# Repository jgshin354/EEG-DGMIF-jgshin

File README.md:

# EEG-DGMIF-jgshin
 EEG-DGMIF-jgshin

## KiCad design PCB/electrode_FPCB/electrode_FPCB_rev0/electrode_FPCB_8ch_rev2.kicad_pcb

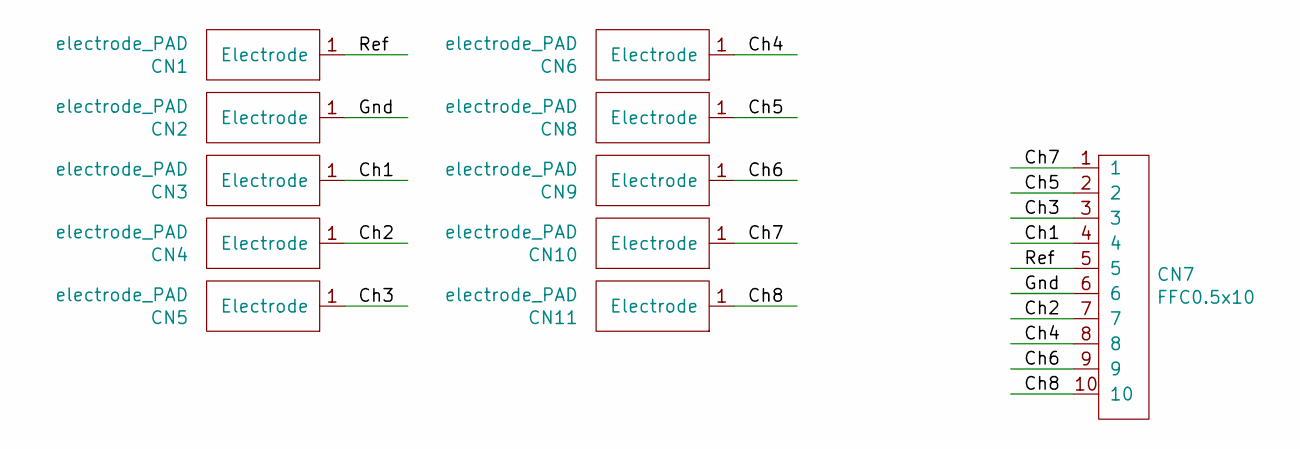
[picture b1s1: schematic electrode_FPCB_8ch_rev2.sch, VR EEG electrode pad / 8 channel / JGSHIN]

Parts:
CN1, CN2, CN3, CN4, CN5, CN6, CN8, CN9, CN10, CN11: electrode_PAD
CN7: FFC0.5x10; FFC cable 0.5 x 10

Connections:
/Ch1: CN3.1, CN7.4
/Ch2: CN4.1, CN7.7
/Ch3: CN5.1, CN7.3
/Ch4: CN6.1, CN7.8
/Ch5: CN7.2, CN8.1
/Ch6: CN7.9, CN9.1
/Ch7: CN7.1, CN10.1
/Ch8: CN7.10, CN11.1
/Gnd: CN2.1, CN7.6
/Ref: CN1.1, CN7.5

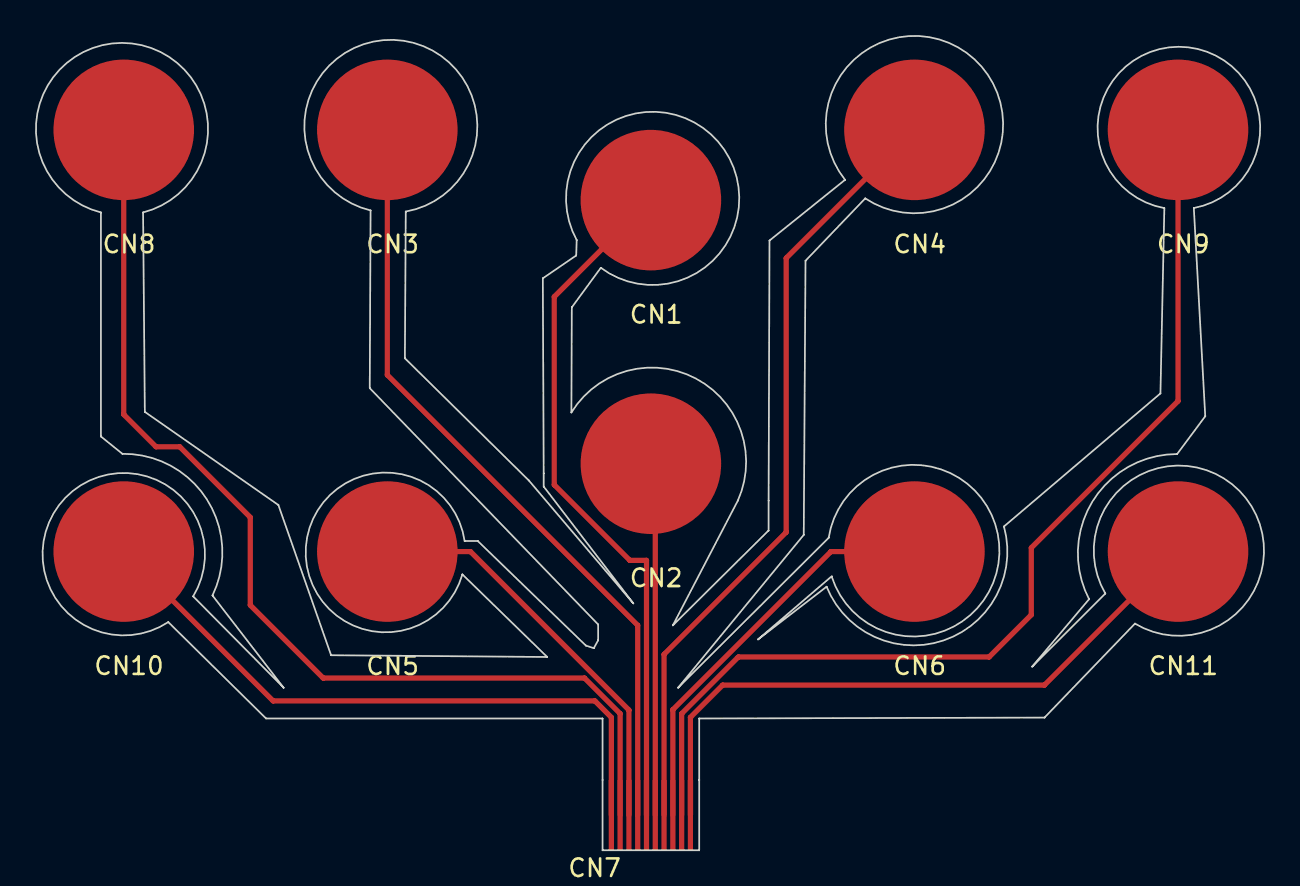
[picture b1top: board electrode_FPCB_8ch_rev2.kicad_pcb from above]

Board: 2 copper layers, 69.9 x 46.3 mm, 11 parts (0 on the bottom side), 10 nets.

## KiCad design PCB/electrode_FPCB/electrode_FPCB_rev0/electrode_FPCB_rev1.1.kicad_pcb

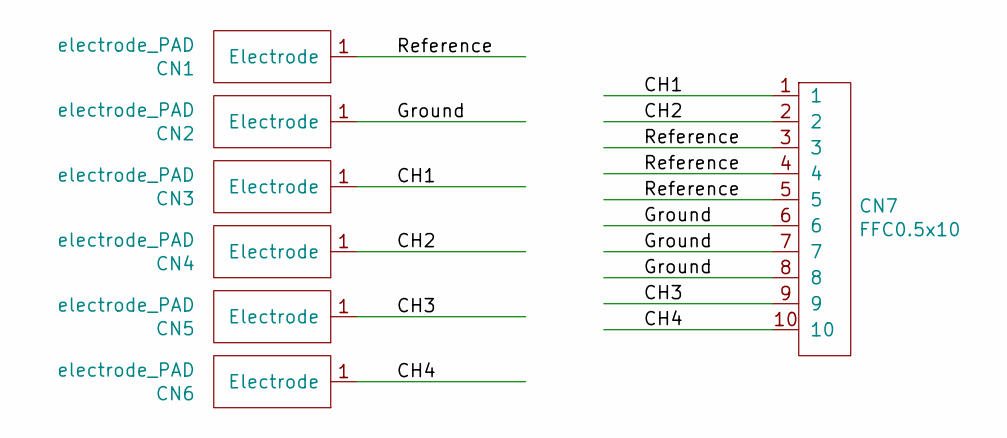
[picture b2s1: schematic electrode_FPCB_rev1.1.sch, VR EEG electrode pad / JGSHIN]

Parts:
CN1, CN2, CN3, CN4, CN5, CN6: electrode_PAD
CN7: FFC0.5x10; FFC cable 0.5 x 10

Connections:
/CH1: CN3.1, CN7.1
/CH2: CN4.1, CN7.2
/CH3: CN5.1, CN7.9
/CH4: CN6.1, CN7.10
/Ground: CN2.1, CN7.6, CN7.7, CN7.8
/Reference: CN1.1, CN7.3, CN7.4, CN7.5

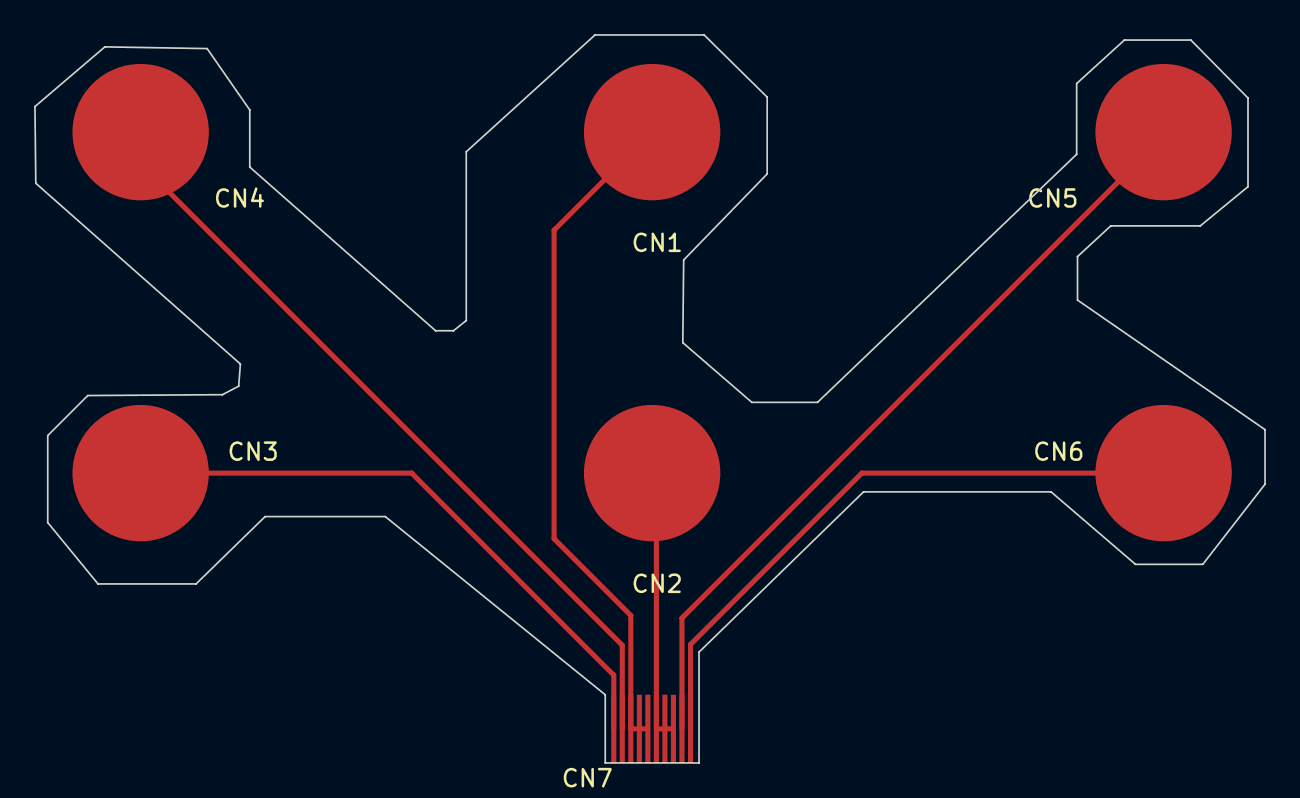
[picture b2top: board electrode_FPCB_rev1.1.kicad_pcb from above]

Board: 2 copper layers, 72.2 x 42.7 mm, 7 parts (0 on the bottom side), 6 nets.

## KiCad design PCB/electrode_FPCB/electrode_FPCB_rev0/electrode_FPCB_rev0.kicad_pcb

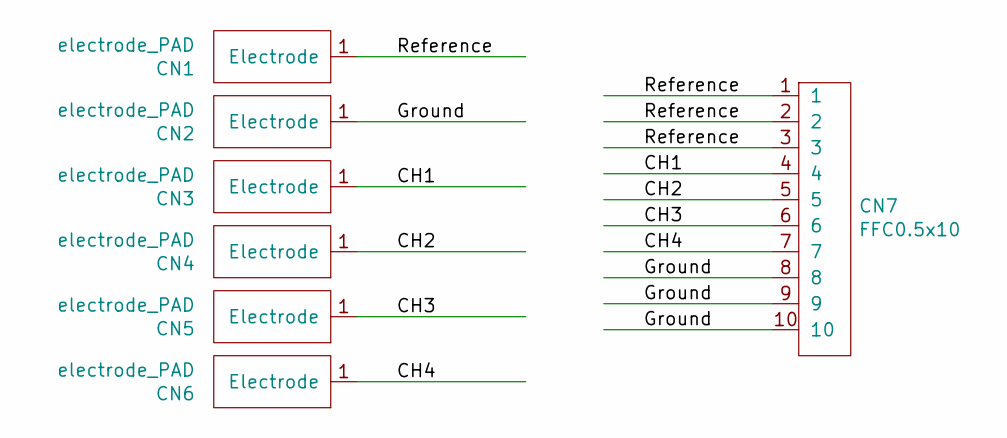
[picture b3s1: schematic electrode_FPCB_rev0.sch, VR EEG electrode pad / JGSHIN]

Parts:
CN1, CN2, CN3, CN4, CN5, CN6: electrode_PAD
CN7: FFC0.5x10; FFC cable 0.5 x 10

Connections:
/CH1: CN3.1, CN7.4
/CH2: CN4.1, CN7.5
/CH3: CN5.1, CN7.6
/CH4: CN6.1, CN7.7
/Ground: CN2.1, CN7.8, CN7.9, CN7.10
/Reference: CN1.1, CN7.1, CN7.2, CN7.3

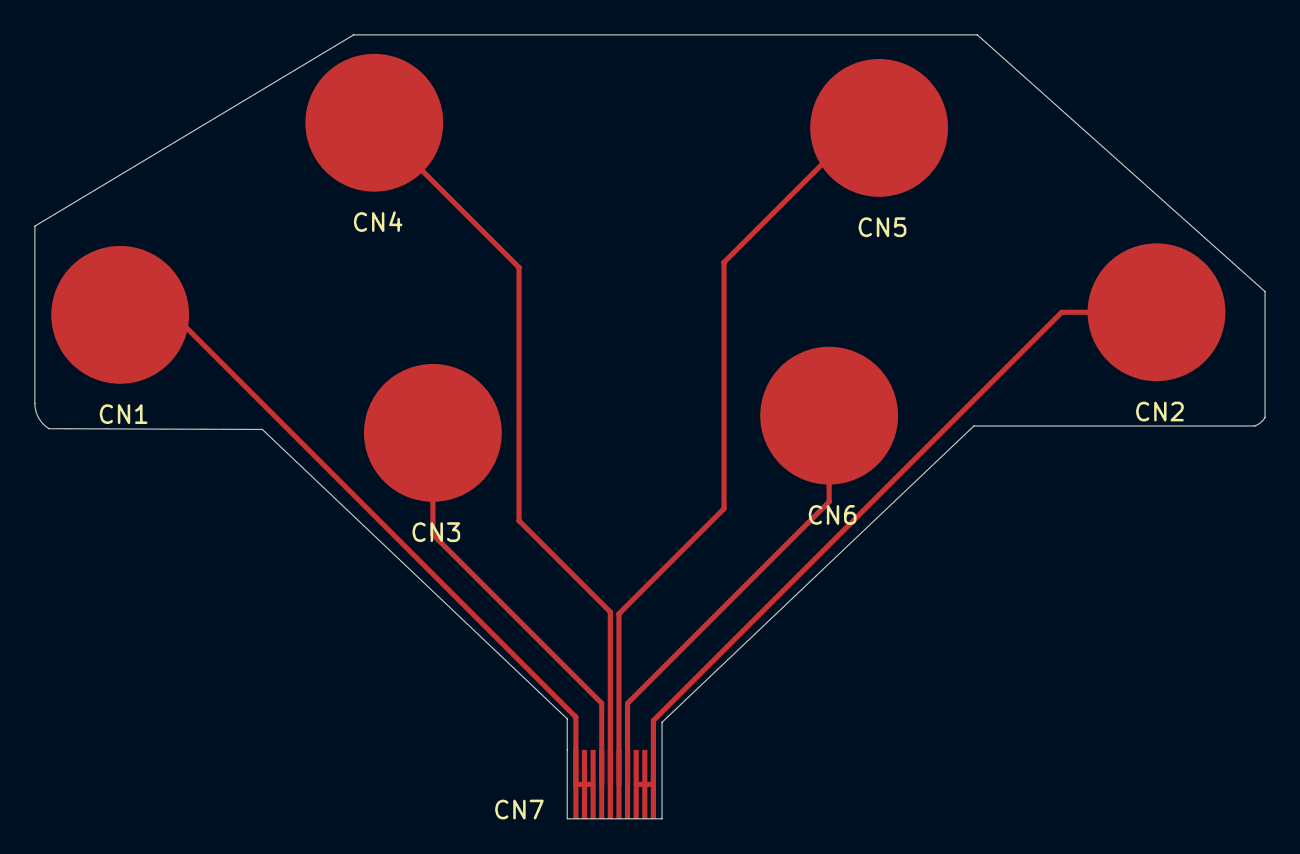
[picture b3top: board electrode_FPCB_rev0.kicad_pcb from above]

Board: 2 copper layers, 71.4 x 45.5 mm, 7 parts (0 on the bottom side), 6 nets.

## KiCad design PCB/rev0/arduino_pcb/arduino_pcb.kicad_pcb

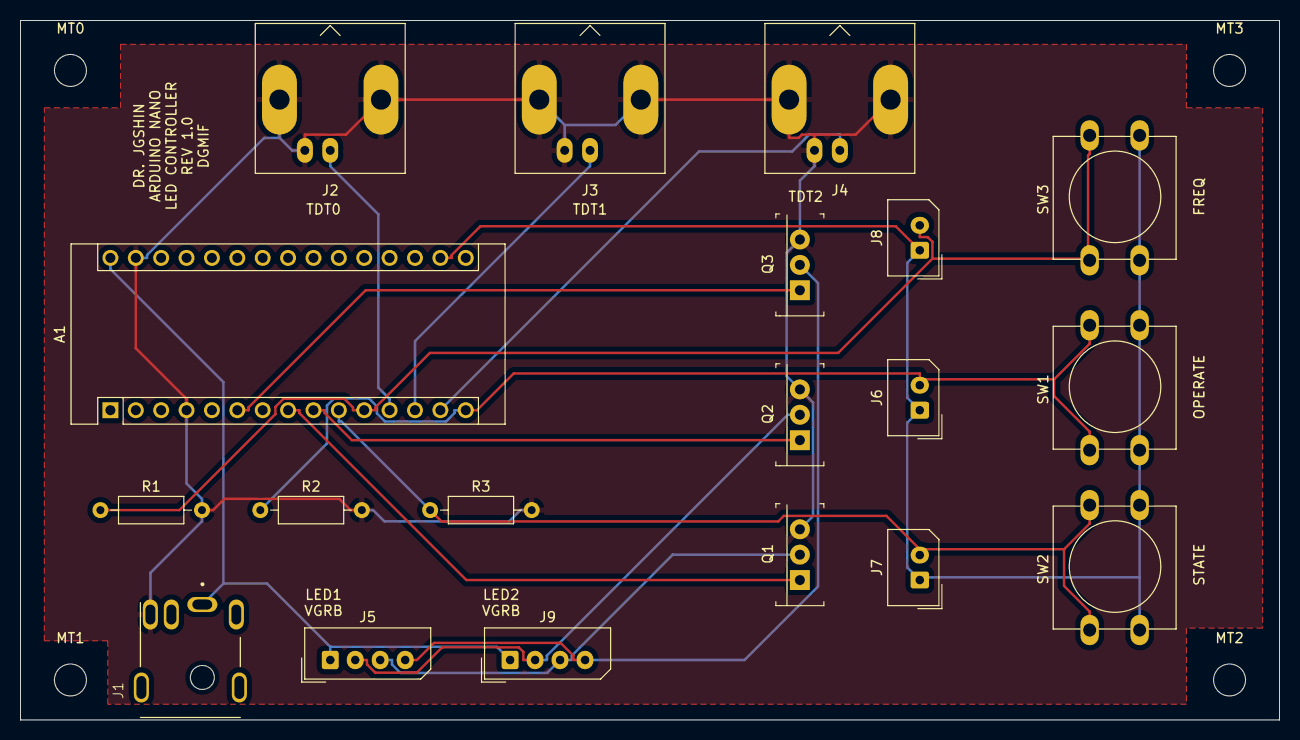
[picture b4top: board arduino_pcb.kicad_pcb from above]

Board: 2 copper layers, 126.0 x 70.0 mm, 23 parts (0 on the bottom side), 15 nets.

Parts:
A1: Arduino_Nano_v3.x; Arduino_Nano
J1: Jack-DC; CUI_PJ-076
J2: TDT0; BNC_Amphenol_B6252HB-NPP3G-50_Horizontal
J3: TDT1; BNC_Amphenol_B6252HB-NPP3G-50_Horizontal
J4: TDT2; BNC_Amphenol_B6252HB-NPP3G-50_Horizontal
J5: LED1; Molex_SPOX_5267-04A_1x04_P2.50mm_Vertical
J6: OPERATE; Molex_SPOX_5267-02A_1x02_P2.50mm_Vertical
J7: STATE; Molex_SPOX_5267-02A_1x02_P2.50mm_Vertical
J8: FREQ; Molex_SPOX_5267-02A_1x02_P2.50mm_Vertical
J9: LED2; Molex_SPOX_5267-04A_1x04_P2.50mm_Vertical
MT0, MT1, MT2, MT3: MountingHole_3.2mm_M3
Q1, Q2, Q3: IRF510PBF; TO-220-3
R1, R2, R3: 4.7K; R_Axial_DIN0207_L6.3mm_D2.5mm_P10.16mm_Horizontal
SW1: OPERATE; SW_PUSH-12mm
SW2: STATE; SW_PUSH-12mm
SW3: FREQ; SW_PUSH-12mm

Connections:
+3V3: A1.17, J6.1, J7.1, J8.1, SW1.2, SW2.2, SW3.2
+12V: A1.30, J1.1, J5.1, J9.1
/BLUELED: J5.4, J9.4, Q3.2
/BLUEPIN: A1.6, Q3.1
/FREQ: A1.11, J8.2, R1.1, SW3.1
/GREENLED: J5.2, J9.2, Q2.2
/GREENPIN: A1.9, Q2.1
/OPERATE: A1.15, J6.2, R2.1, SW1.1
/REDLED: J5.3, J9.3, Q1.2
/REDPIN: A1.8, Q1.1
/STATE: A1.10, J7.2, R3.1, SW2.1
/TDTPIN0: A1.12, J2.1
/TDTPIN1: A1.13, J3.1
/TDTPIN2: A1.14, J4.1
GND: A1.4, A1.29, J1.2, J2.2, J3.2, J4.2, Q1.3, Q2.3, Q3.3, R1.2, R2.2, R3.2

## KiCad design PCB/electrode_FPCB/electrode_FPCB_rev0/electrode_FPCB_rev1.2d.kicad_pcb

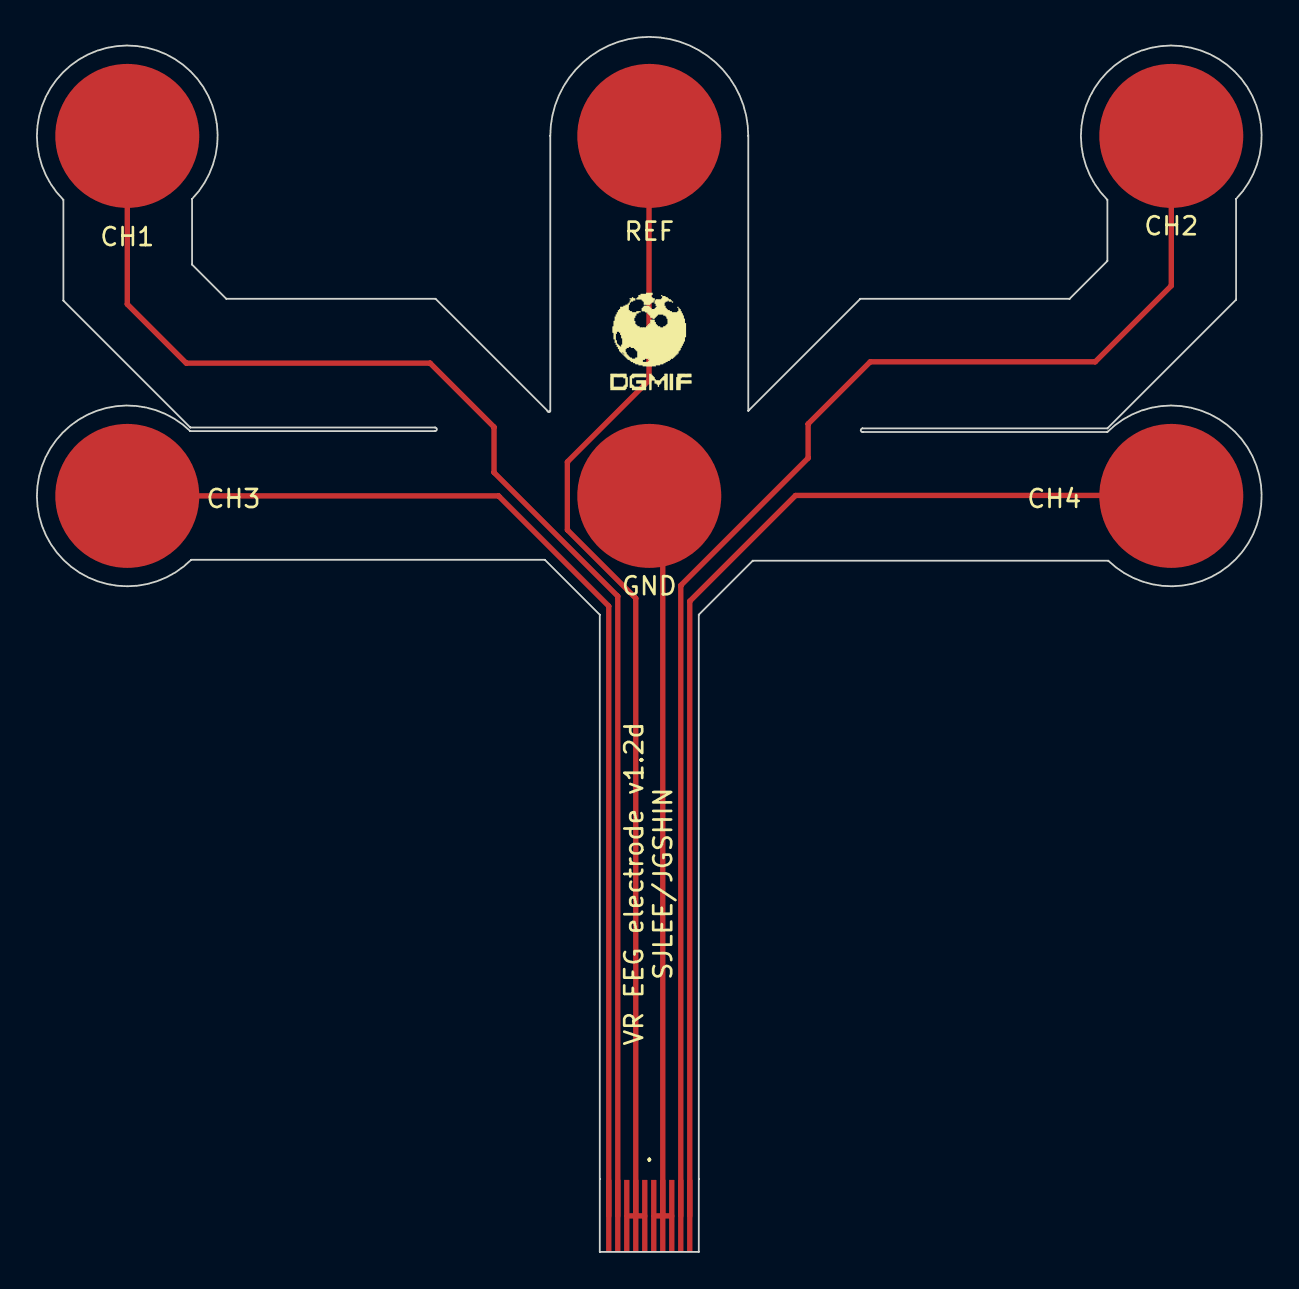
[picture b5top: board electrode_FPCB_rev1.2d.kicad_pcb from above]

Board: 2 copper layers, 68.0 x 67.5 mm, 8 parts (0 on the bottom side), 6 nets.

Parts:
 : DGMIF-CI_5mm
.: FFC0.5x10; FFC cable 0.5 x 10
CH1, CH2, CH3, CH4: electrode_PAD
GND: electrode_PAD
REF: electrode_PAD

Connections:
/CH1: ..2, CH1.1
/CH2: ..9, CH2.1
/CH3: ..1, CH3.1
/CH4: ..10, CH4.1
/Ground: ..6, ..7, ..8, GND.1
/Reference: ..3, ..4, ..5, REF.1

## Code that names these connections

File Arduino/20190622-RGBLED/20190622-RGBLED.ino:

#define REDPIN 5
#define GREENPIN 6
#define BLUEPIN 3
//#define RST 2 //jgshin Add
#define STATE 7 //jgshin Add
#define OPERATE 12 // jgshin ADD
#define TDTPIN0 9
#define TDTPIN1 10 //jgshin Add
#define TDTPIN2 11 //jgshin Add
//0h: LED off
//1h: green PW, 2h: green CW
//3h: red PW,   4h: red CW
//5h: blue PW,  6h: blue CW 

void setup() {
  pinMode(REDPIN, OUTPUT);
  pinMode(GREENPIN, OUTPUT);
  pinMode(BLUEPIN, OUTPUT);
  pinMode(TDTPIN0, OUTPUT);
  pinMode(TDTPIN1, OUTPUT);
  pinMode(TDTPIN2, OUTPUT);
//  pinMode(RST, INPUT);
  pinMode(STATE, INPUT);
  pinMode(OPERATE, INPUT);
  digitalWrite(REDPIN, LOW);
  digitalWrite(GREENPIN, LOW);
  digitalWrite(BLUEPIN, LOW);
}

//boolean bRST = false;
boolean bSTATE = false;
boolean bOPERATE = false;
int state_n = 0; // 0: Green, 1: Red, 2: Blue 
int out_pin = GREENPIN;

int count=0;
int frequency=40; //Unit: Hz, it should be over 1 Hz.
int treatment_time=10; //Unit: sec.
int count_limit=treatment_time*frequency;
int trigger_time=500; //Unit: msec.
int number_subexp=10; //(Number_subexp) times ON/OFF
int number_subexp_count=0;


void loop() {
  if(digitalRead(STATE) == HIGH){
    if(bSTATE == false){
      bSTATE = true;
      state_n = (state_n + 1) % 3;
      stateRef();
    }
  }
  else{
    bSTATE = false;
  }


  if(digitalRead(OPERATE) == HIGH){
    if(bOPERATE == false){
      bOPERATE = true;
      operationCode();
      endRef();
    }
  }
  else{
    bOPERATE = false;
  }
}

void operationCode()
{
}


void stateRef()
{
  switch(state_n){
    case 0: out_pin = GREENPIN;  break;
    case 1: out_pin = REDPIN;    break;
    case 2: out_pin = BLUEPIN;   break;
    default:out_pin = GREENPIN;  break;
  }
  
  if(state_n == 0) {     //green blinking
    for (int i = 0; i < 3; i++) {
      digitalWrite(out_pin, HIGH);
      delay(100);
      digitalWrite(out_pin, LOW);
      delay(100);
    }
  } 
}


void endRef()
{
  if(state_n == 0){     //green blinking
    for (int i = 0; i < 5; i++) {
      digitalWrite(out_pin, HIGH);
      delay(500);
      digitalWrite(out_pin, LOW);
      delay(500);
    }
  }
}




/*
int count=0;
int frequency=40; //Unit: Hz, it should be over 1 Hz.
int treatment_time=10; //Unit: sec.
int count_limit=treatment_time*frequency;
int trigger_time=500; //Unit: msec.
int number_subexp=10; //(Number_subexp) times ON/OFF
int number_subexp_count=0;




void loop() {
  while(number_subexp_count<number_subexp) {
    analogWrite(TDTPIN, 0); //TDT trigger ON to mark START time
    //delay(trigger_time);
    //analogWrite(TDTPIN, 0); //TDT trigger 0.5 sec

    analogWrite(REDPIN, 255); //Red LED ON
    analogWrite(GREENPIN, 0); 
    analogWrite(BLUEPIN, 0);

    delay(treatment_time*1000);

    analogWrite(REDPIN, 0); //Red LED OFF
    analogWrite(GREENPIN, 0);
    analogWrite(BLUEPIN, 0);
      
    //analogWrite(TDTPIN, 255); //TDT trigger ON to mark END time
    //delay(trigger_time);
    analogWrite(TDTPIN, 255); //TDT trigger 0.5 sec

    delay(treatment_time*1000);

    count=0; //counter reset
    number_subexp_count++;
  }
}
*/

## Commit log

2020-06-16 Regular Commit
    Regular Commit
2020-06-16 regular
    regualr commit
2020-06-16 Regular Commit
    Filename rename
2020-06-18 Regular Commit`
    Montage Upload
2020-06-22 Arduino code pending
    arduino LED control code pending
2020-06-22 Arduino Commit pending
    Arduino Commit pending
2020-06-23 Update 20190622-RGBLED.ino
    Arduino LED Controller code
2020-06-24 Arduino freqency variation code commit
2020-06-24 freeCAD start
2020-06-24 gx file creation
2020-06-24 3rd printing
2020-06-25 electrode 2nd ver
2020-06-25 electrode_pad 3
2020-07-24 Update Electrode_pad
    Acrylic Electrode Pads
2020-08-03 PCB making starts
2020-08-03 PCB_rev0
2020-08-04 PCB_gerber update
2020-08-20 Create Acrylic_LED_pad
2020-10-08 2nd trial 20200924
2020-10-30 Leeno_pin_electrode_pad
2020-10-30 G050 edit
2020-10-30 Leeno-electropad rev2
2020-11-12 G105R rev3b 9/7 channel pad
2021-02-22 20190622-RGBLED.ino update
    20190622-RGBLED.ino update
2021-06-02 G105 9ch EEG pad rev4
2021-06-07 20210607 mouse test prep.
2021-06-23 ElectrodePad update
2021-07-05 adding VC_DLL
2021-07-05 adding VS_DLL_Gen
2021-07-06 DLL code update
2021-07-07 Debugging, EEG_Quantization_v0_1
2021-07-07 editing vi file name
2021-07-13 Cage program / 20Min program for experiment
2021-07-26 FPCB rev1.0
2021-07-26 VR Electroce v1.1
2021-07-26 EEG electrode v2.0
    8 channel FPCB EEG electrode
2021-07-27 EEG FPCB rev1.1 gerber
2021-08-02 VR EEG electrode pad v1.2c
2021-08-02 VR EEG electrode pad v1.2d
2021-08-02 vr electrode pad v1.2d (fix silkscreen)
2021-08-26 minor changes
